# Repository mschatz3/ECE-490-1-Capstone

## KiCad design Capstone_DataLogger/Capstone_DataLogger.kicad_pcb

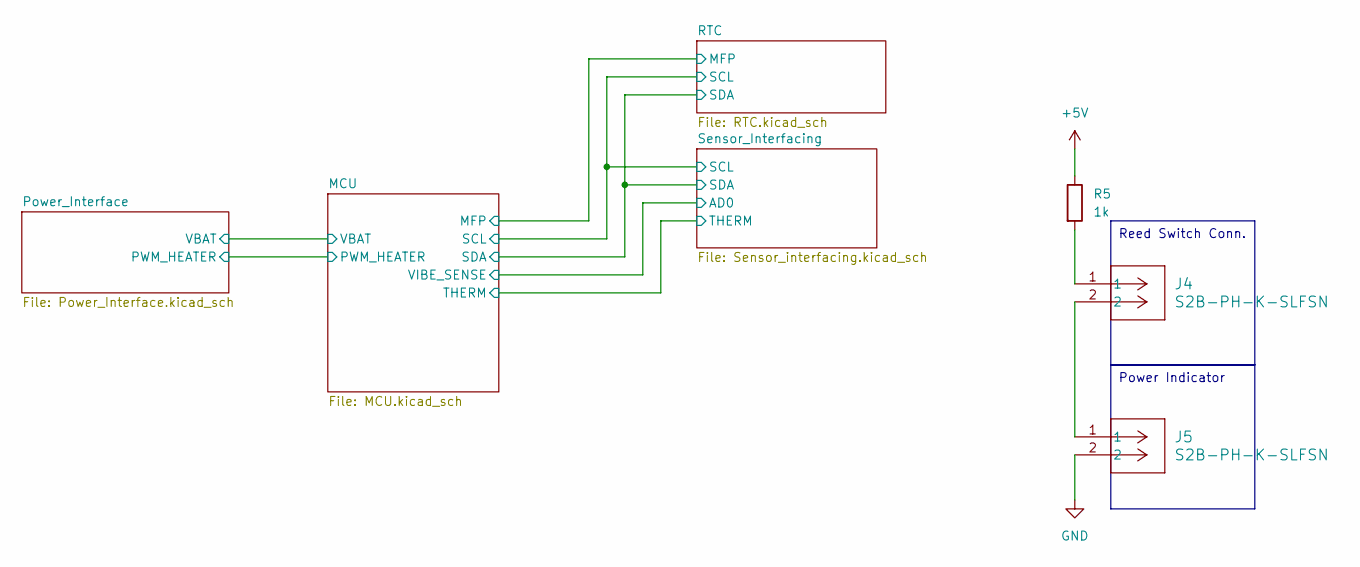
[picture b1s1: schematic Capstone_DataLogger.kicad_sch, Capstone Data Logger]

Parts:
J4, J5: S2B-PH-K-SLFSN; CONN_B2B-XH-A_JST
R5: 1k; R_1206_3216Metric_Pad1.30x1.75mm_HandSolder

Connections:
+5V: R5.1; also elsewhere on the board
GND: J5.2; also elsewhere on the board
unnamed: J4.1, R5.2
unnamed: J4.2, J5.1

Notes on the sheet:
Power Indicator
Reed Switch Conn.

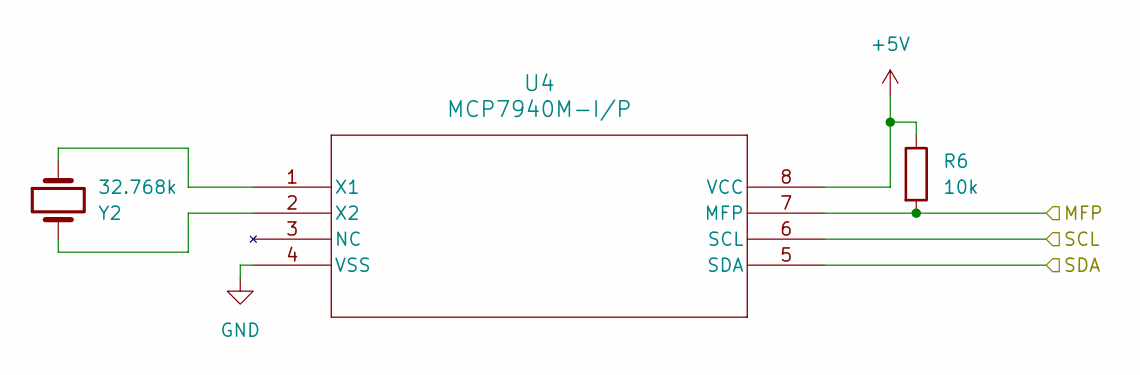
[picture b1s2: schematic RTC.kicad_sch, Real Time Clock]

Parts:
R6: 10k; R_1206_3216Metric_Pad1.30x1.75mm_HandSolder
U4: MCP7940M-I/P; PDIP8_300MC_MCH
Y2: 32.768k; Cylindrical Can, Radial

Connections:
+5V: R6.1, U4.8 (VCC); also elsewhere on the board
/MCU/MFP: R6.2, U4.7 (MFP); also elsewhere on the board
/MCU/SCL: U4.6 (SCL); also elsewhere on the board
/MCU/SDA: U4.5 (SDA); also elsewhere on the board
GND: U4.4 (VSS); also elsewhere on the board
unnamed: U4.1 (X1), Y2.1
unnamed: U4.2 (X2), Y2.2

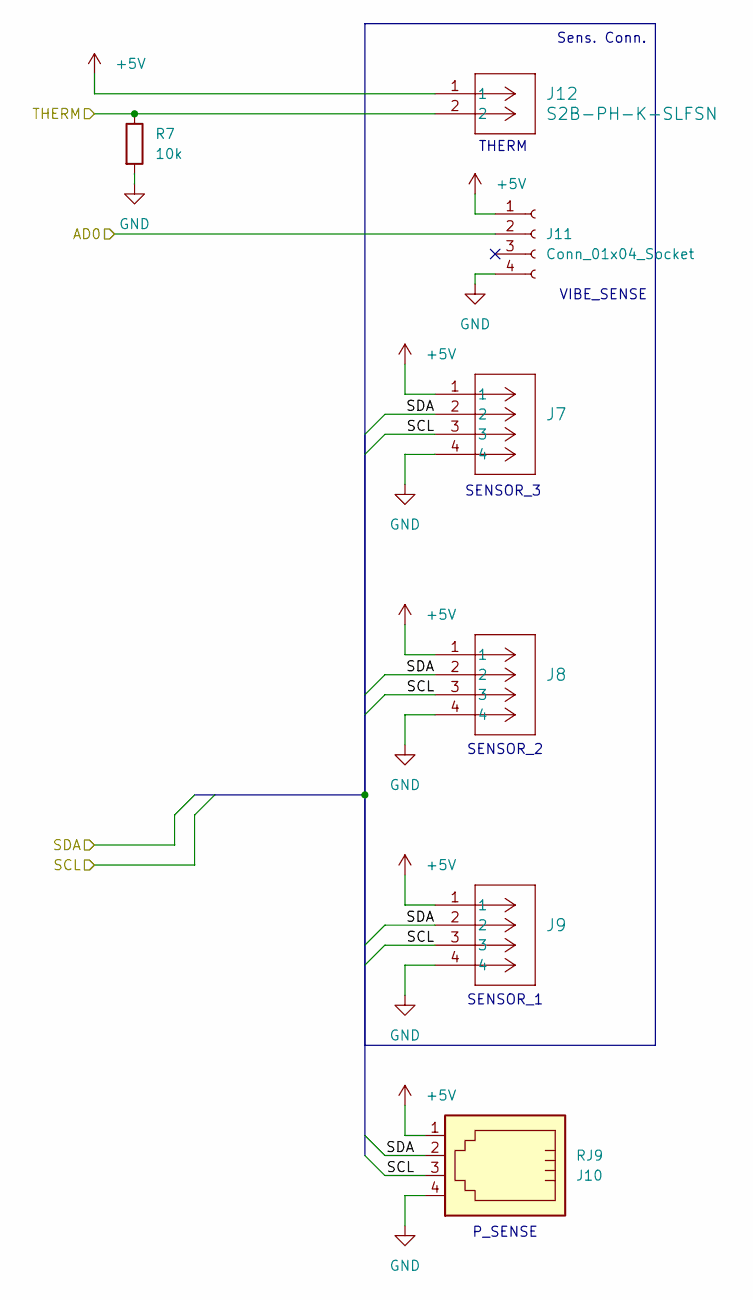
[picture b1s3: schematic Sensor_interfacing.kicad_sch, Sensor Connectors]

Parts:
J7, J8, J9: S4B-PH-K-SLFSN; CONN_B4B-XH-A_JST
J10: RJ9
J11: Conn_01x04_Socket; PinSocket_1x04_P2.54mm_Horizontal
J12: S2B-PH-K-SLFSN; CONN_B2B-XH-A_JST
R7: 10k; R_1206_3216Metric_Pad1.30x1.75mm_HandSolder

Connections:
+5V: J7.1, J8.1, J9.1, J10.1, J11.1, J12.1; also elsewhere on the board
/MCU/SCL: J7.3, J8.3, J9.3, J10.3; also elsewhere on the board
/MCU/SDA: J7.2, J8.2, J9.2, J10.2; also elsewhere on the board
/MCU/THERM: J12.2, R7.1; also elsewhere on the board
/MCU/VIBE_SENSE: J11.2; also elsewhere on the board
GND: J7.4, J8.4, J9.4, J10.4, J11.4, R7.2; also elsewhere on the board

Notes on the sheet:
Sens. Conn.
P_SENSE
SENSOR_2
SENSOR_1
VIBE_SENSE
THERM
SENSOR_3

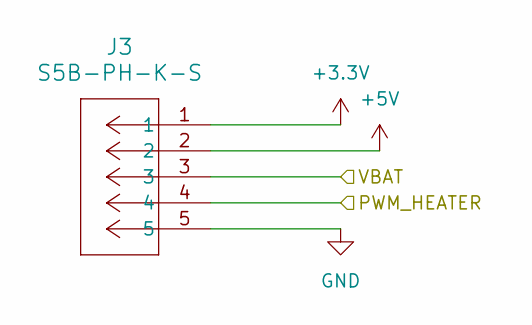
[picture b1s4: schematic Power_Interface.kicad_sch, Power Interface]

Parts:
J3: S5B-PH-K-S; CONN_B5B-XH-A_JST

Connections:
+3.3V: J3.1; also elsewhere on the board
+5V: J3.2; also elsewhere on the board
/MCU/PWM_HEATER: J3.4; also elsewhere on the board
/MCU/VBAT: J3.3; also elsewhere on the board
GND: J3.5; also elsewhere on the board

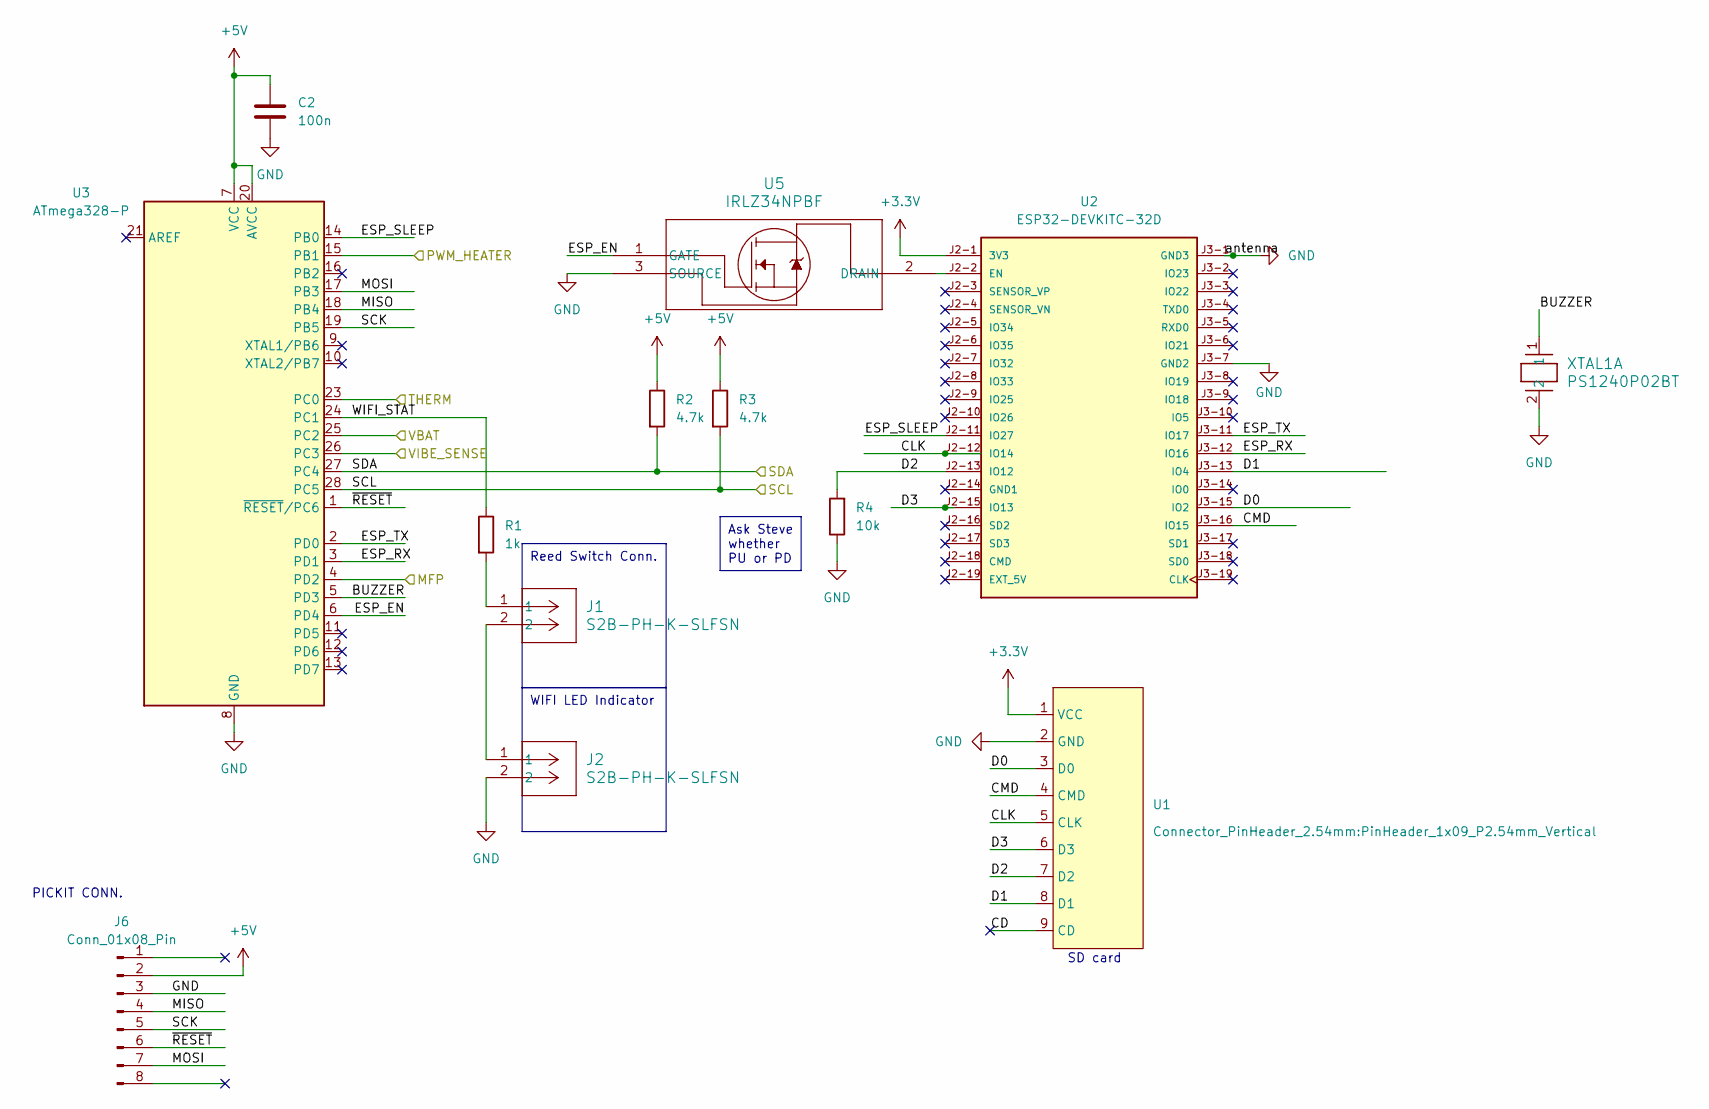
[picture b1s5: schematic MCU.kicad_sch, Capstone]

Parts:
C2: 100n; C_1206_3216Metric_Pad1.33x1.80mm_HandSolder
J1, J2: S2B-PH-K-SLFSN; CONN_B2B-XH-A_JST
J6: Conn_01x08_Pin; PinHeader_1x08_P2.54mm_Vertical
R1: 1k; R_1206_3216Metric_Pad1.30x1.75mm_HandSolder
R2, R3: 4.7k; R_1206_3216Metric_Pad1.30x1.75mm_HandSolder
R4: 10k; R_1206_3216Metric_Pad1.30x1.75mm_HandSolder
U1: PinHeader_1x09_P2.54mm_Vertical
U2: ESP32-DEVKITC-32D; MODULE_ESP32-DEVKITC-32D; PARTREV V4
U3: ATmega328-P; DIP-28_W7.62mm
U5: IRLZ34NPBF; TO-220AB_INF
XTAL1: PS1240P02BT; XTAL_PS1240P02BT_TDK

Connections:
+3.3V: U1.1 (VCC), U2.J2-1 (3V3); also elsewhere on the board
+5V: C2.1, J6.2, R2.1, R3.1, U3.7 (VCC), U3.20 (AVCC); also elsewhere on the board
/MCU/BUZZER: U3.5 (PD3), XTAL1.1
/MCU/CD: U1.9 (CD)
/MCU/CLK: U1.5 (CLK), U2.J2-12 (IO14)
/MCU/CMD: U1.4 (CMD), U2.J3-16 (IO15)
/MCU/D0: U1.3 (D0), U2.J3-15 (IO2)
/MCU/D1: U1.8 (D1), U2.J3-13 (IO4)
/MCU/D2: R4.2, U1.7 (D2), U2.J2-13 (IO12)
/MCU/D3: U1.6 (D3), U2.J2-15 (IO13)
/MCU/ESP_EN: U3.6 (PD4), U5.1 (GATE)
/MCU/ESP_RX: U2.J3-12 (IO16), U3.3 (PD1)
/MCU/ESP_SLEEP: U2.J2-11 (IO27), U3.14 (PB0)
/MCU/ESP_TX: U2.J3-11 (IO17), U3.2 (PD0)
/MCU/MFP: U3.4 (PD2); also elsewhere on the board
/MCU/MISO: J6.4, U3.18 (PB4)
/MCU/MOSI: J6.7, U3.17 (PB3)
/MCU/PWM_HEATER: U3.15 (PB1); also elsewhere on the board
/MCU/SCK: J6.5, U3.19 (PB5)
/MCU/SCL: R3.2, U3.28 (PC5); also elsewhere on the board
/MCU/SDA: R2.2, U3.27 (PC4); also elsewhere on the board
/MCU/THERM: U3.23 (PC0); also elsewhere on the board
/MCU/VBAT: U3.25 (PC2); also elsewhere on the board
/MCU/VIBE_SENSE: U3.26 (PC3); also elsewhere on the board
/MCU/WIFI_STAT: R1.1, U3.24 (PC1)
/MCU/~RESET: J6.6, U3.1 (~RESET/PC6)
GND: C2.2, J2.2, J6.3, R4.1, U1.2 (GND), U2.J3-1 (GND3), U2.J3-7 (GND2), U3.8 (GND), U3.22 (GND), U5.3 (SOURCE), XTAL1.2; also elsewhere on the board
unnamed: J1.1, R1.2
unnamed: J1.2, J2.1
unnamed: U2.J2-2 (EN), U5.2 (DRAIN)

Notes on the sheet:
Reed Switch Conn.
WIFI LED Indicator
Ask Steve whether PU or PD
PICKIT CONN.
SD card

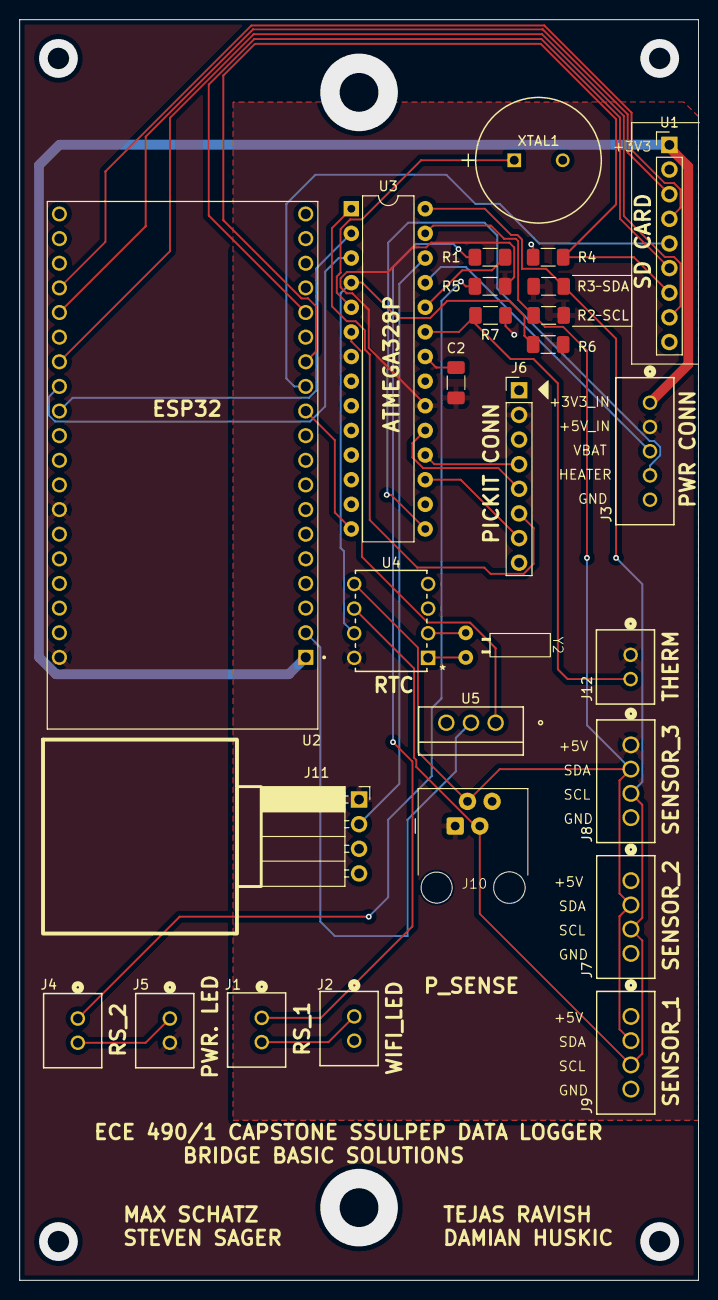
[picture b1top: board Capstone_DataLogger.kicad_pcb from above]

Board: 2 copper layers, 70.0 x 130.0 mm, 27 parts (0 on the bottom side), 33 nets.

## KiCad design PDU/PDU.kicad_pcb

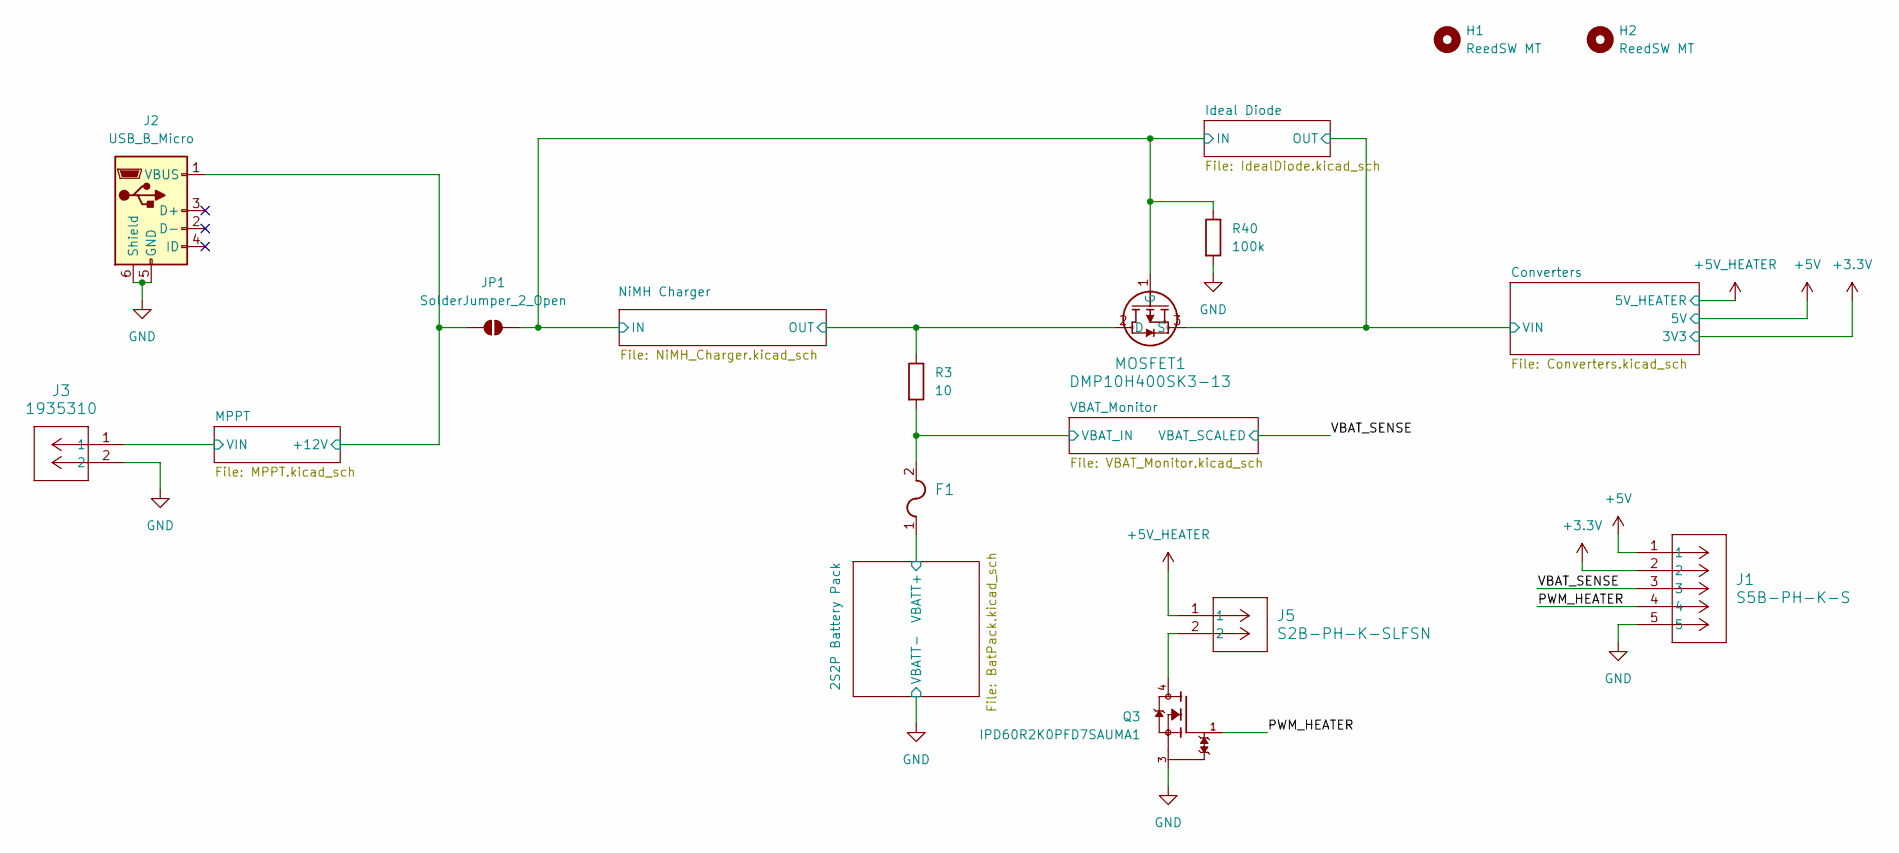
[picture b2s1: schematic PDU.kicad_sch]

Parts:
F1: 39212000000; Fuse_2920_7451Metric_Pad2.10x5.45mm_HandSolder
H1, H2: ReedSW MT; ReedSW
J1: S5B-PH-K-S; CONN_B5B-XH-A_JST
J2: USB_B_Micro; USB_Micro-B_Amphenol_10104110_Horizontal
J3: 1935310; CONN_1935310_PXC
J5: S2B-PH-K-SLFSN; CONN_S2B-PH-K-S_JST
JP1: SolderJumper_2_Open; SolderJumper-2_P1.3mm_Open_TrianglePad1.0x1.5mm
MOSFET1: DMP10H400SK3-13; TO252-DPAK-DMP10H400SK3_DIO
Q3: IPD60R2K0PFD7SAUMA1; DPAK229P994X240-3N; PARTREV 02
R3: 10; R_2512_6332Metric_Pad1.40x3.35mm_HandSolder
R40: 100k; R_1206_3216Metric_Pad1.30x1.75mm_HandSolder

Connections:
+3.3V: J1.2; also elsewhere on the board
+5V: J1.1; also elsewhere on the board
+5V_HEATER: J5.1; also elsewhere on the board
/2S2P Battery Pack/VBATT+: F1.1; also elsewhere on the board
/Converters/VIN: MOSFET1.3 (S); also elsewhere on the board
/Ideal Diode/IN: JP1.2 (B), MOSFET1.1 (G), R40.1; also elsewhere on the board
/MPPT/+12V: J2.1 (VBUS), JP1.1 (A); also elsewhere on the board
/MPPT/VIN: J3.1; also elsewhere on the board
/NiMH Charger/OUT: MOSFET1.2 (D), R3.1; also elsewhere on the board
/PWM_HEATER: J1.4, Q3.1
/VBAT_Monitor/VBAT_IN: F1.2, R3.2; also elsewhere on the board
/VBAT_SENSE: J1.3; also elsewhere on the board
GND: J1.5, J2.5 (GND), J2.6 (Shield), J3.2, Q3.3, R40.2; also elsewhere on the board
unnamed: J5.2, Q3.4

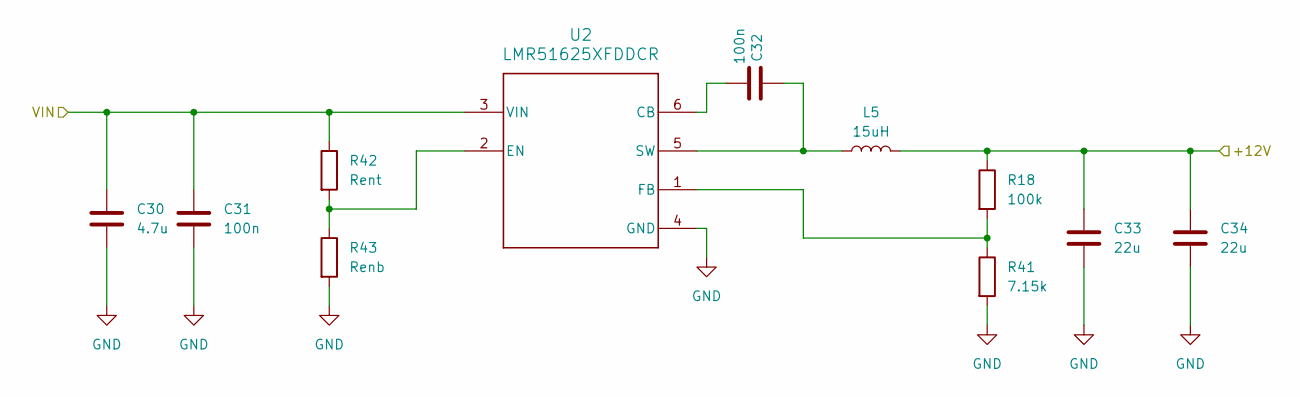
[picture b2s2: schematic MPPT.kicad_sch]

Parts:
C30: 4.7u; C_1206_3216Metric_Pad1.33x1.80mm_HandSolder
C31, C32: 100n; C_1206_3216Metric_Pad1.33x1.80mm_HandSolder
C33, C34: 22u; C_1206_3216Metric_Pad1.33x1.80mm_HandSolder
L5: 15uH; IND_BOURNS_SRR1208
R18: 100k; R_1206_3216Metric_Pad1.30x1.75mm_HandSolder
R41: 7.15k; R_1206_3216Metric_Pad1.30x1.75mm_HandSolder
R42: Rent; R_1206_3216Metric_Pad1.30x1.75mm_HandSolder
R43: Renb; R_1206_3216Metric_Pad1.30x1.75mm_HandSolder
U2: LMR51625XFDDCR; DDC0006A-MFG

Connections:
/MPPT/+12V: C33.1, C34.1, L5.2, R18.1; also elsewhere on the board
/MPPT/VIN: C30.1, C31.1, R42.1, U2.3 (VIN); also elsewhere on the board
GND: C30.2, C31.2, C33.2, C34.2, R41.2, R43.2, U2.4 (GND); also elsewhere on the board
unnamed: C32.2, U2.6 (CB)
unnamed: R42.2, R43.1, U2.2 (EN)
unnamed: R18.2, R41.1, U2.1 (FB)
unnamed: C32.1, L5.1, U2.5 (SW)

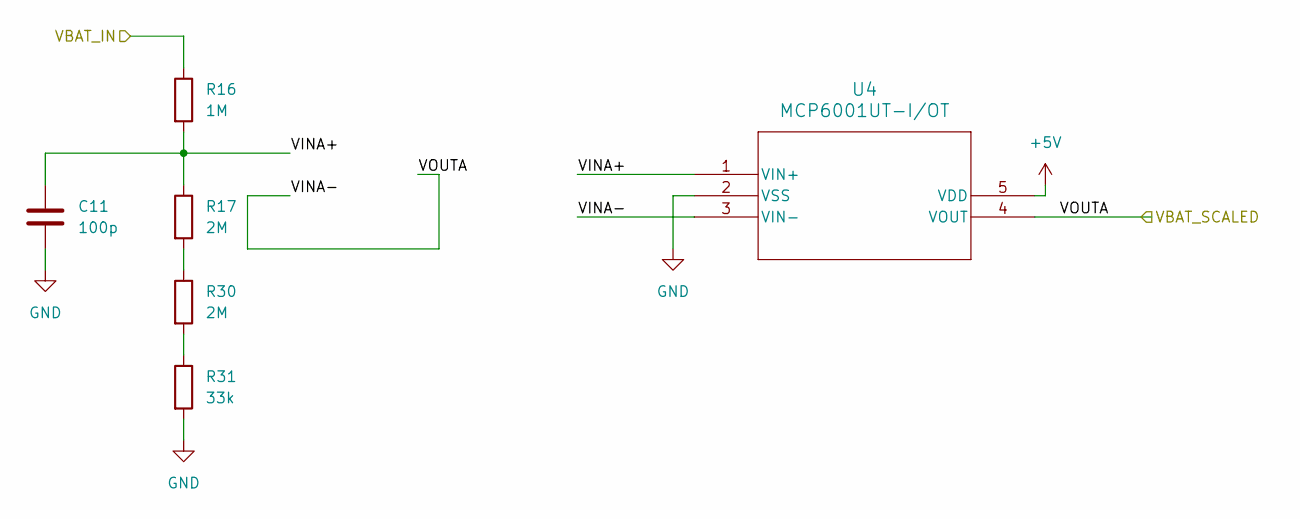
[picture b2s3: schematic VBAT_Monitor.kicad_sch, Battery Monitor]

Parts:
C11: 100p; C_1206_3216Metric_Pad1.33x1.80mm_HandSolder
R16: 1M; R_1206_3216Metric_Pad1.30x1.75mm_HandSolder
R17, R30: 2M; R_1206_3216Metric_Pad1.30x1.75mm_HandSolder
R31: 33k; R_1206_3216Metric_Pad1.30x1.75mm_HandSolder
U4: MCP6001UT-I/OT; SOT-23-5_MC_MCH

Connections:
+5V: U4.5 (VDD); also elsewhere on the board
/VBAT_Monitor/VBAT_IN: R16.1; also elsewhere on the board
/VBAT_Monitor/VINA+: C11.1, R16.2, R17.1, U4.1 (VIN+)
/VBAT_SENSE: U4.3 (VIN-), U4.4 (VOUT); also elsewhere on the board
GND: C11.2, R31.2, U4.2 (VSS); also elsewhere on the board
unnamed: R17.2, R30.1
unnamed: R30.2, R31.1

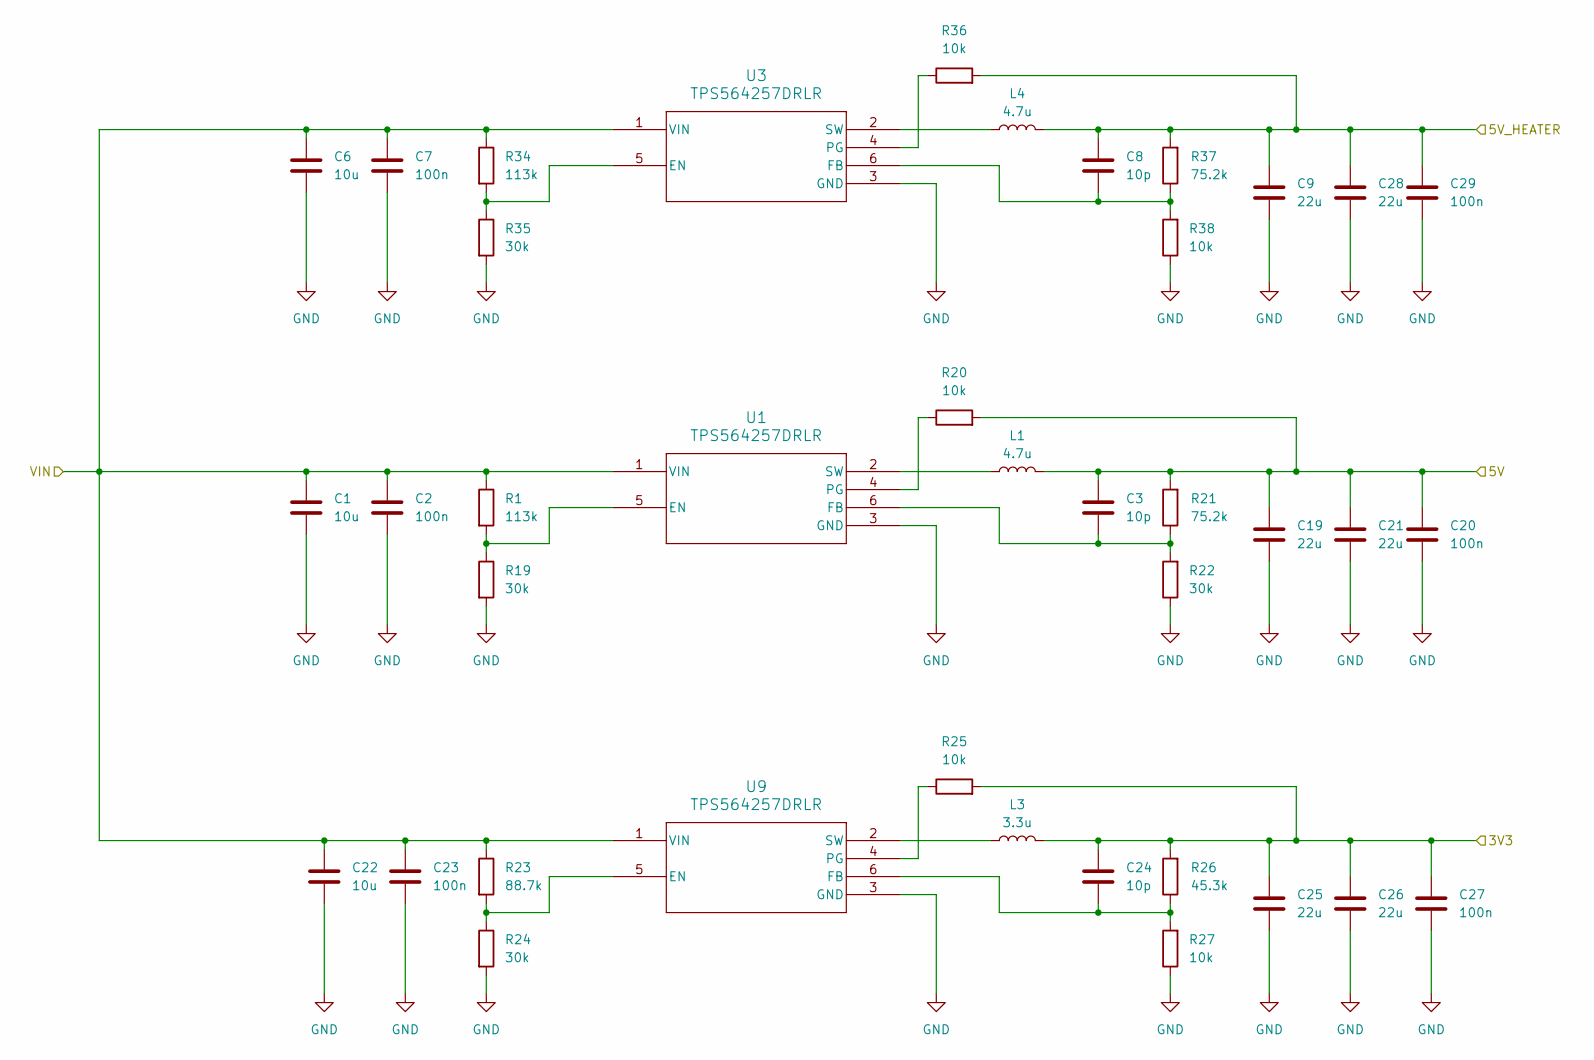
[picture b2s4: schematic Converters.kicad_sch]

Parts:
C1, C6, C22: 10u; C_1206_3216Metric_Pad1.33x1.80mm_HandSolder
C2, C7, C20, C23, C29: 100n; C_1206_3216Metric_Pad1.33x1.80mm_HandSolder
C3, C8: 10p; R_1206_3216Metric_Pad1.30x1.75mm_HandSolder
C9, C19, C21, C25, C26, C28: 22u; C_1206_3216Metric_Pad1.33x1.80mm_HandSolder
C24: 10p; C_1206_3216Metric_Pad1.33x1.80mm_HandSolder
C27: 100n; R_1206_3216Metric_Pad1.30x1.75mm_HandSolder
L1, L4: 4.7u; L_Bourns_SRP7028A_7.3x6.6mm
L3: 3.3u; IND_IHLP-4040DZ_VIS
R1, R34: 113k; R_1206_3216Metric_Pad1.30x1.75mm_HandSolder
R19, R22, R24, R35: 30k; R_1206_3216Metric_Pad1.30x1.75mm_HandSolder
R20, R25, R27, R36, R38: 10k; R_1206_3216Metric_Pad1.30x1.75mm_HandSolder
R21, R37: 75.2k; R_1206_3216Metric_Pad1.30x1.75mm_HandSolder
R23: 88.7k; R_1206_3216Metric_Pad1.30x1.75mm_HandSolder
R26: 45.3k; R_1206_3216Metric_Pad1.30x1.75mm_HandSolder
U1, U3, U9: TPS564257DRLR; TPS564242DRLR_TEX

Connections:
+3.3V: C24.1, C25.1, C26.1, C27.1, L3.2, R25.2, R26.2; also elsewhere on the board
+5V: C3.1, C19.1, C20.1, C21.1, L1.2, R20.2, R21.2; also elsewhere on the board
+5V_HEATER: C8.1, C9.1, C28.1, C29.1, L4.2, R36.2, R37.2; also elsewhere on the board
/Converters/VIN: C1.1, C2.1, C6.1, C7.1, C22.1, C23.1, R1.1, R23.1, R34.1, U1.1 (VIN), U3.1 (VIN), U9.1 (VIN); also elsewhere on the board
GND: C1.2, C2.2, C6.2, C7.2, C9.2, C19.2, C20.2, C21.2, C22.2, C23.2, C25.2, C26.2, C27.2, C28.2, C29.2, R19.2, R22.1, R24.2, R27.1, R35.2, R38.1, U1.3 (GND), U3.3 (GND), U9.3 (GND); also elsewhere on the board
unnamed: R1.2, R19.1, U1.5 (EN)
unnamed: C3.2, R21.1, R22.2, U1.6 (FB)
unnamed: R20.1, U1.4 (PG)
unnamed: L1.1, U1.2 (SW)
unnamed: R34.2, R35.1, U3.5 (EN)
unnamed: C8.2, R37.1, R38.2, U3.6 (FB)
unnamed: R36.1, U3.4 (PG)
unnamed: L4.1, U3.2 (SW)
unnamed: R23.2, R24.1, U9.5 (EN)
unnamed: C24.2, R26.1, R27.2, U9.6 (FB)
unnamed: R25.1, U9.4 (PG)
unnamed: L3.1, U9.2 (SW)

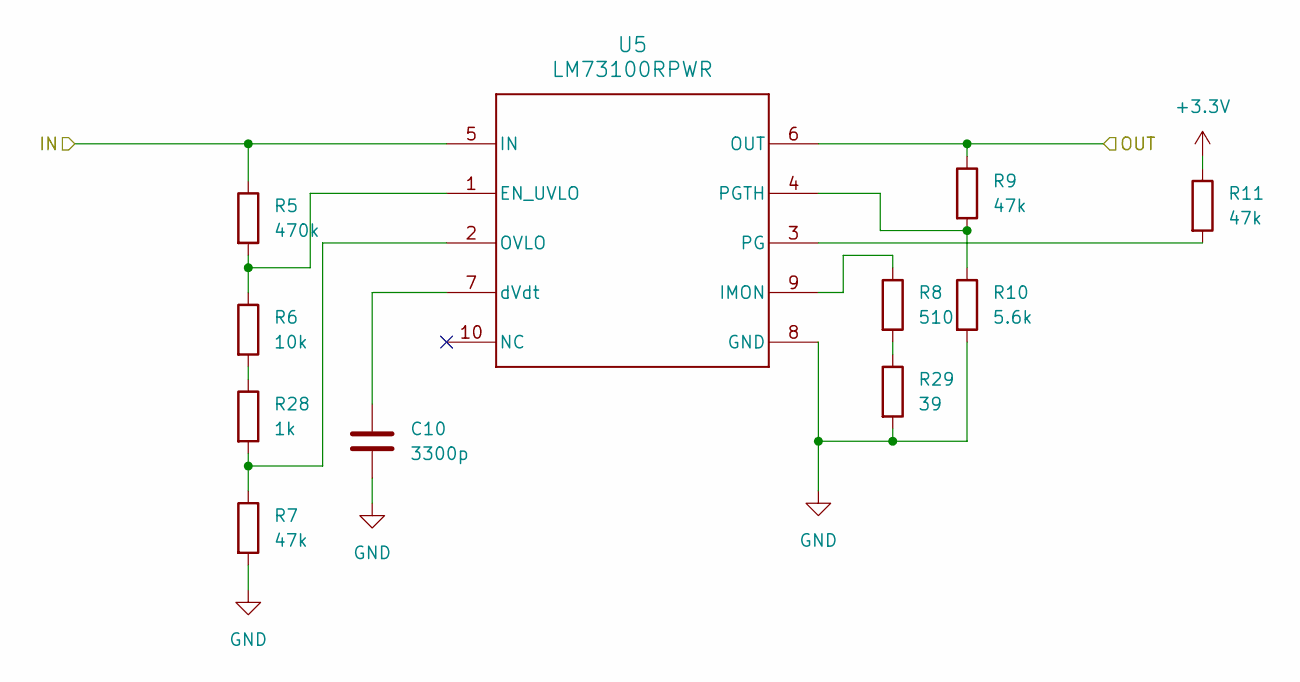
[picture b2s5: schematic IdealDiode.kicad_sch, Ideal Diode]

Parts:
C10: 3300p; C_1206_3216Metric_Pad1.33x1.80mm_HandSolder
R5: 470k; R_1206_3216Metric_Pad1.30x1.75mm_HandSolder
R6: 10k; C_1206_3216Metric_Pad1.33x1.80mm_HandSolder
R7, R9, R11: 47k; R_1206_3216Metric_Pad1.30x1.75mm_HandSolder
R8: 510; R_1206_3216Metric_Pad1.30x1.75mm_HandSolder
R10: 5.6k; R_1206_3216Metric_Pad1.30x1.75mm_HandSolder
R28: 1k; R_1206_3216Metric_Pad1.30x1.75mm_HandSolder
R29: 39; R_1206_3216Metric_Pad1.30x1.75mm_HandSolder
U5: LM73100RPWR; RPW0010A-MFG

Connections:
+3.3V: R11.1; also elsewhere on the board
/Converters/VIN: R9.1, U5.6 (OUT); also elsewhere on the board
/Ideal Diode/IN: R5.1, U5.5 (IN); also elsewhere on the board
GND: C10.2, R7.2, R10.2, R29.2, U5.8 (GND); also elsewhere on the board
unnamed: R6.2, R28.1
unnamed: R8.2, R29.1
unnamed: R5.2, R6.1, U5.1 (EN_UVLO)
unnamed: R8.1, U5.9 (IMON)
unnamed: R7.1, R28.2, U5.2 (OVLO)
unnamed: R11.2, U5.3 (PG)
unnamed: R9.2, R10.1, U5.4 (PGTH)
unnamed: C10.1, U5.7 (dVdt)

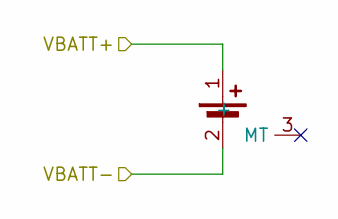
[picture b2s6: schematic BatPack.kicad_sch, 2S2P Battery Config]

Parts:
M1: AA_Bat_Contact

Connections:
/2S2P Battery Pack/VBATT+: M1.1 (+); also elsewhere on the board
GND: M1.2 (-); also elsewhere on the board

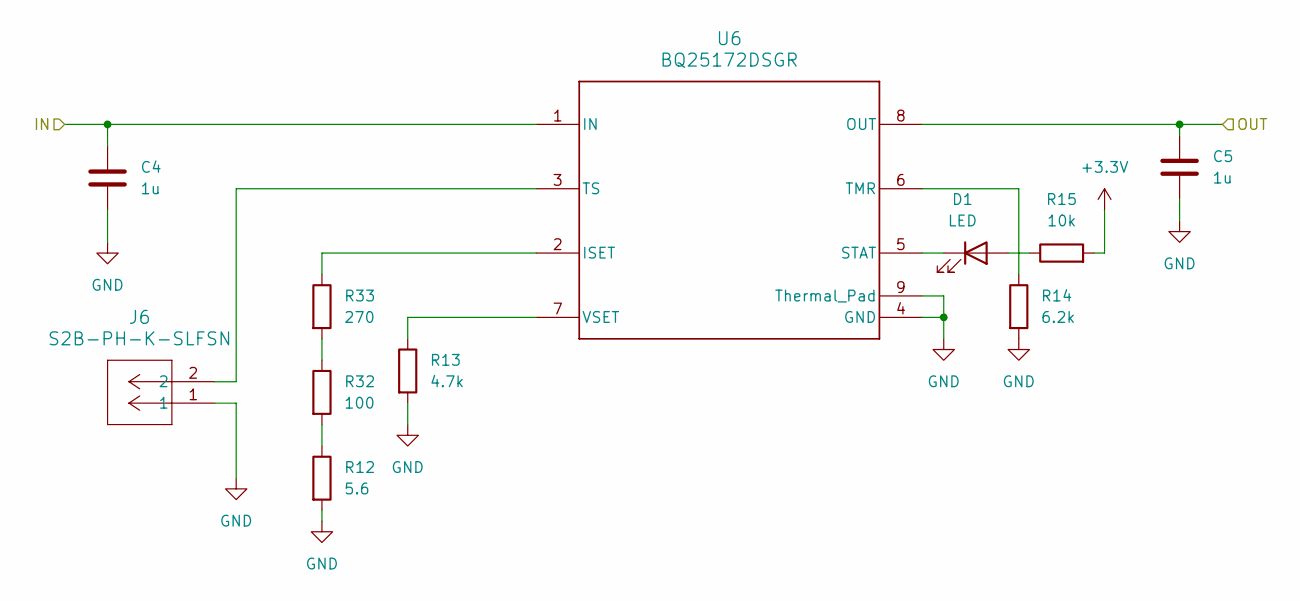
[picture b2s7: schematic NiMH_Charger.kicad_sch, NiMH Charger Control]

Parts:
C4, C5: 1u; C_1206_3216Metric_Pad1.33x1.80mm_HandSolder
D1: LED; D_1206_3216Metric_Pad1.42x1.75mm_HandSolder
J6: S2B-PH-K-SLFSN; CONN_S2B-PH-K-S_JST
R12: 5.6; R_1206_3216Metric_Pad1.30x1.75mm_HandSolder
R13: 4.7k; R_1206_3216Metric_Pad1.30x1.75mm_HandSolder
R14: 6.2k; R_1206_3216Metric_Pad1.30x1.75mm_HandSolder
R15: 10k; R_1206_3216Metric_Pad1.30x1.75mm_HandSolder
R32: 100; R_1206_3216Metric_Pad1.30x1.75mm_HandSolder
R33: 270; R_1206_3216Metric_Pad1.30x1.75mm_HandSolder
U6: BQ25172DSGR; DSG0008A-IPC_A

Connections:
+3.3V: R15.2; also elsewhere on the board
/Ideal Diode/IN: C4.1, U6.1 (IN); also elsewhere on the board
/NiMH Charger/OUT: C5.1, U6.8 (OUT); also elsewhere on the board
GND: C4.2, C5.2, J6.1, R12.2, R13.2, R14.2, U6.4 (GND), U6.9 (Thermal_Pad); also elsewhere on the board
unnamed: D1.2 (A), R15.1
unnamed: D1.1 (K), U6.5 (STAT)
unnamed: R12.1, R32.2
unnamed: R32.1, R33.2
unnamed: R33.1, U6.2 (ISET)
unnamed: R14.1, U6.6 (TMR)
unnamed: J6.2, U6.3 (TS)
unnamed: R13.1, U6.7 (VSET)

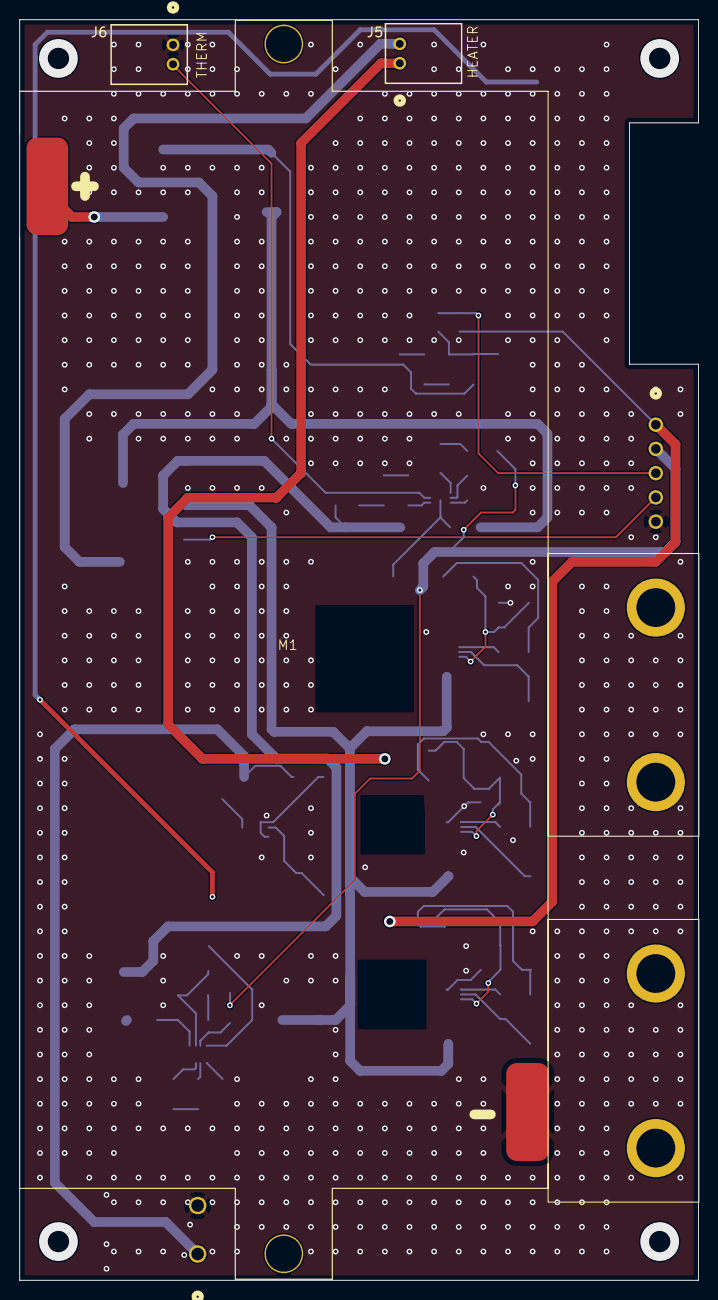
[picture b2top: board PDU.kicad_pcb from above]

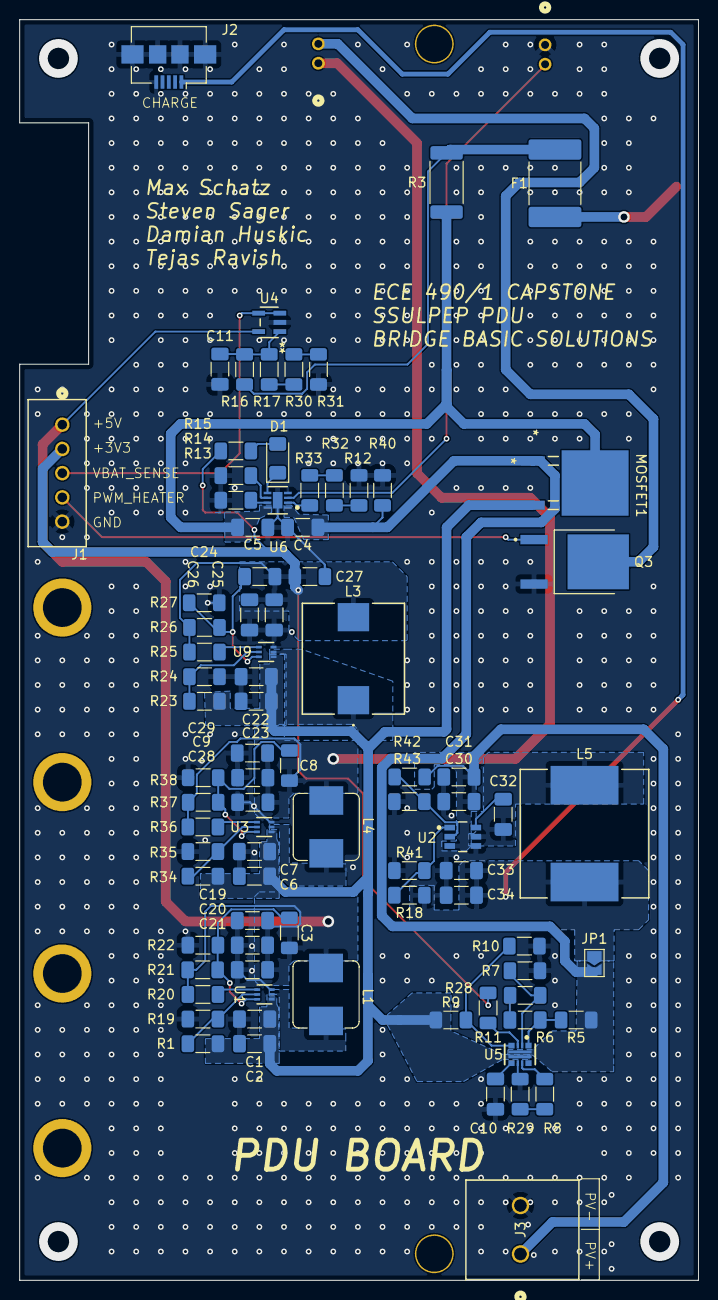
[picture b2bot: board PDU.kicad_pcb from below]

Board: 2 copper layers, 70.0 x 130.0 mm, 91 parts (86 on the bottom side), 49 nets.

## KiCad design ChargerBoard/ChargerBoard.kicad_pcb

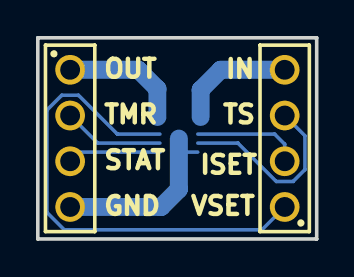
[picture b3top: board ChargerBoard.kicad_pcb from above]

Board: 2 copper layers, 15.5 x 11.2 mm, 3 parts (1 on the bottom side), 7 nets.

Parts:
J1, J2: 61300411121
U1: BQ25172DSGR; DSG0008A-IPC_A

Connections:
/GND: J1.4, U1.4 (GND), U1.9 (Thermal_Pad)
/IN: J2.2, J2.4, U1.1 (IN), U1.2 (ISET)
/OUT: J1.1, U1.8 (OUT)
/STAT: J1.3, U1.5 (STAT)
/TMR: J1.2, U1.6 (TMR)
/TS: J2.3, U1.3 (TS)
/VSET: J2.1, U1.7 (VSET)

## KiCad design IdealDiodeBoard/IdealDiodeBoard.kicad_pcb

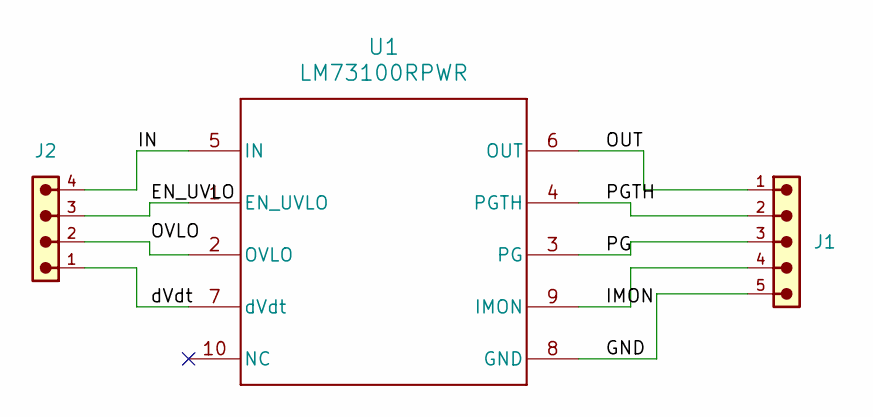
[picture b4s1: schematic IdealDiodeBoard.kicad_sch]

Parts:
J1: 61300511121; PART-NUMBER 61300511121
J2: 61300411121; PART-NUMBER 61300411121
U1: LM73100RPWR; RPW0010A-MFG

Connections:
/EN_UVLO: J2.3, U1.1 (EN_UVLO)
/GND: J1.5, U1.8 (GND)
/IMON: J1.4, U1.9 (IMON)
/IN: J2.4, U1.5 (IN)
/OUT: J1.1, U1.6 (OUT)
/OVLO: J2.2, U1.2 (OVLO)
/PG: J1.3, U1.3 (PG)
/PGTH: J1.2, U1.4 (PGTH)
/dVdt: J2.1, U1.7 (dVdt)

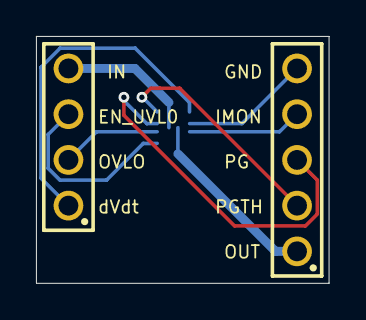
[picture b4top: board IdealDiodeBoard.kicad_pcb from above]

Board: 2 copper layers, 16.3 x 13.7 mm, 3 parts (1 on the bottom side), 9 nets.

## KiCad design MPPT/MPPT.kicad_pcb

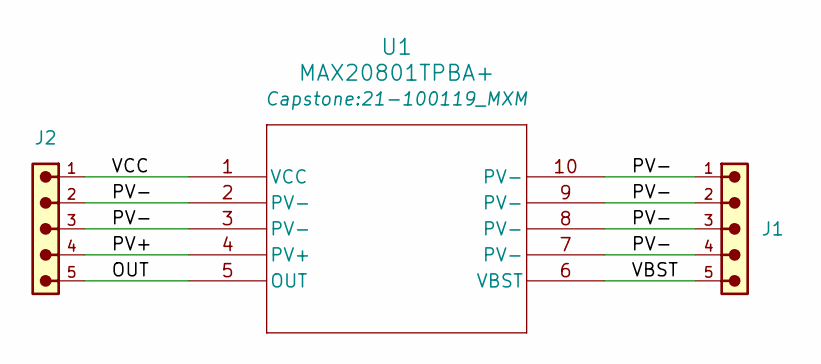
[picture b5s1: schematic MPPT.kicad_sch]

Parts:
J1, J2: 61300511121; PART-NUMBER 61300511121
U1: MAX20801TPBA+; 21-100119_MXM

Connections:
/OUT: J2.5, U1.5 (OUT)
/PV+: J2.4, U1.4 (PV+)
/PV-: J1.1, J1.2, J1.3, J1.4, J2.2, J2.3, U1.2 (PV-), U1.3 (PV-), U1.7 (PV-), U1.8 (PV-), U1.9 (PV-), U1.10 (PV-)
/VBST: J1.5, U1.6 (VBST)
/VCC: J2.1, U1.1 (VCC)

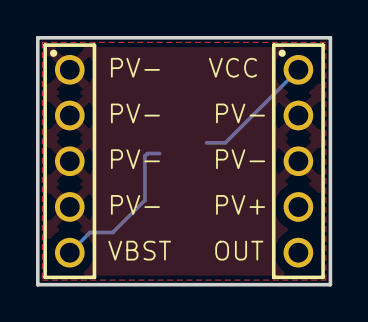
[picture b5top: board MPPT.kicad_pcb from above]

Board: 2 copper layers, 16.3 x 13.7 mm, 3 parts (1 on the bottom side), 5 nets.

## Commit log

2025-01-30 added resistor
2025-01-31 basic changes
2025-02-06 pcb componet placement changed
2025-02-11 pcb connected except SD card
2025-02-11 pcb connections comeleted
2025-02-13 Revised PCB
2025-02-13 Last revision before oreder
2025-02-14 NVM another revision before order, should be good now
2025-02-14 Made revision on PDU board before ECLASS submission
2025-03-08 Hypothetical final revision of datalogger
2025-03-27 Last revision
